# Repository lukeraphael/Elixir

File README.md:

# Elixir

The Elixir is a monoblock ergonomic mechanical keyboard. The design has been greatly inspired by the [Atreus](https://github.com/technomancy/atreus), [Sweep](https://github.com/davidphilipbarr/Sweep) and [Sofle](https://github.com/josefadamcik/SofleKeyboard) keyboards.

## Motivation

The Elixir was born out of a desire to create an 'introductory' ergonomic mechanical keyboard. Its simple and inexpensive construction reduces the time and cost required to get started. Furthermore, it was intentionally made to accomodate most common keycap sets, removing the need to obtain a niche 'ergo' keycap set.

## Features

- Powered by [QMK](https://docs.qmk.fm/#/)
- Fits many cheap standard keycap sets
  - Virtually all uniform profile sets e.g. DSA and XDA
  - Virtually all "full coverage" keycap sets
- 50 keys - just enough to accomodate to new users but few enough to allow users to experience layers, an imperative part of ergo keyboards

## Gallery

## Install firmware
Steps:
1. Copy qmk/keyboards/elixir to your local qmk folder
2. ```qmk flash -kb elixir -km default```
3. Plug in your micro controller and set it to flashing mode (connect reset and ground pins twice)

## License

The Elixir Keyboard is licensed under [Creative Commons Attribution-NonCommercial 4.0 International License](https://creativecommons.org/licenses/by-nc/4.0).

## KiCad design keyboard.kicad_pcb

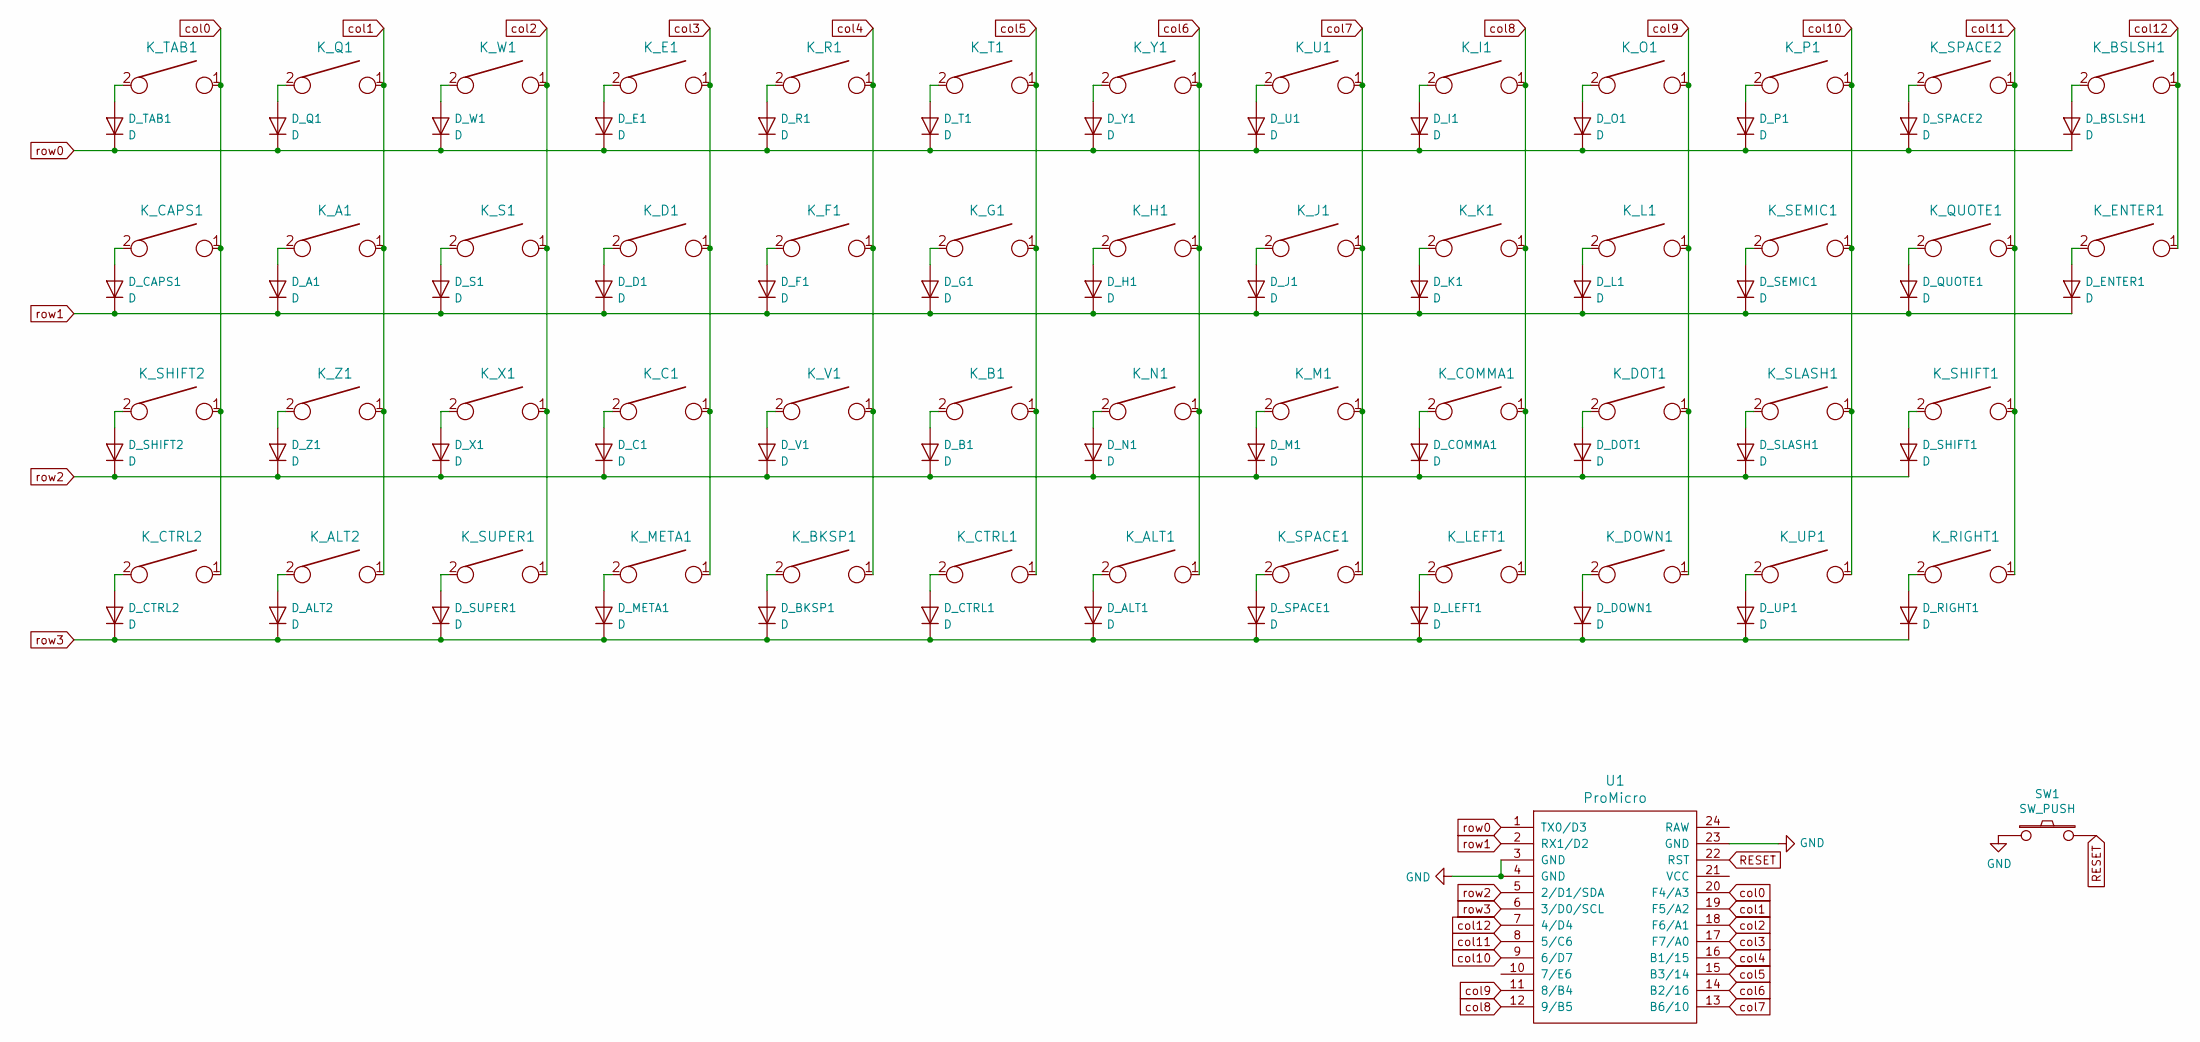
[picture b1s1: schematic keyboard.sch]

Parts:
D_A1: D; D_SOD123_axial
D_ALT1, D_ALT2: D; D_SOD123_axial
D_B1: D; D_SOD123_axial
D_BKSP1: D; D_SOD123_axial
D_BSLSH1: D; D_SOD123_axial
D_C1: D; D_SOD123_axial
D_CAPS1: D; D_SOD123_axial
D_COMMA1: D; D_SOD123_axial
D_CTRL1, D_CTRL2: D; D_SOD123_axial
D_D1: D; D_SOD123_axial
D_DOT1: D; D_SOD123_axial
D_DOWN1: D; D_SOD123_axial
D_E1: D; D_SOD123_axial
D_ENTER1: D; D_SOD123_axial
D_F1: D; D_SOD123_axial
D_G1: D; D_SOD123_axial
D_H1: D; D_SOD123_axial
D_I1: D; D_SOD123_axial
D_J1: D; D_SOD123_axial
D_K1: D; D_SOD123_axial
D_L1: D; D_SOD123_axial
D_LEFT1: D; D_SOD123_axial
D_M1: D; D_SOD123_axial
D_META1: D; D_SOD123_axial
D_N1: D; D_SOD123_axial
D_O1: D; D_SOD123_axial
D_P1: D; D_SOD123_axial
D_Q1: D; D_SOD123_axial
D_QUOTE1: D; D_SOD123_axial
D_R1: D; D_SOD123_axial
D_RIGHT1: D; D_SOD123_axial
D_S1: D; D_SOD123_axial
D_SEMIC1: D; D_SOD123_axial
D_SHIFT1, D_SHIFT2: D; D_SOD123_axial
D_SLASH1: D; D_SOD123_axial
D_SPACE1, D_SPACE2: D; D_SOD123_axial
D_SUPER1: D; D_SOD123_axial
D_T1: D; D_SOD123_axial
D_TAB1: D; D_SOD123_axial
D_U1: D; D_SOD123_axial
D_UP1: D; D_SOD123_axial
D_V1: D; D_SOD123_axial
D_W1: D; D_SOD123_axial
D_X1: D; D_SOD123_axial
D_Y1: D; D_SOD123_axial
D_Z1: D; D_SOD123_axial
K_A1: KEYSW; MX-1U
K_ALT1: KEYSW; MX-2U
K_ALT2: KEYSW; MX-1U
K_B1: KEYSW; MX-1U
K_BKSP1: KEYSW; MX-1.25U
K_BSLSH1: KEYSW; MX-1.5U
K_C1: KEYSW; MX-1U
K_CAPS1: KEYSW; MX-1.75U
K_COMMA1: KEYSW; MX-1U
K_CTRL1: KEYSW; MX-2U
K_CTRL2: KEYSW; MX-1.25U
K_D1: KEYSW; MX-1U
K_DOT1: KEYSW; MX-1U
K_DOWN1: KEYSW; MX-1U
K_E1: KEYSW; MX-1U
K_ENTER1: KEYSW; MX-2.25U
K_F1: KEYSW; MX-1U
K_G1: KEYSW; MX-1U
K_H1: KEYSW; MX-1U
K_I1: KEYSW; MX-1U
K_J1: KEYSW; MX-1U
K_K1: KEYSW; MX-1U
K_L1: KEYSW; MX-1U
K_LEFT1: KEYSW; MX-1U
K_M1: KEYSW; MX-1U
K_META1: KEYSW; MX-1U
K_N1: KEYSW; MX-1U
K_O1: KEYSW; MX-1U
K_P1: KEYSW; MX-1U
K_Q1: KEYSW; MX-1U
K_QUOTE1: KEYSW; MX-1U
K_R1: KEYSW; MX-1U
K_RIGHT1: KEYSW; MX-1U
K_S1: KEYSW; MX-1U
K_SEMIC1: KEYSW; MX-1U
K_SHIFT1: KEYSW; MX-2.75U
K_SHIFT2: KEYSW; MX-2.25U
K_SLASH1: KEYSW; MX-1U
K_SPACE1: KEYSW; MX-1.25U
K_SPACE2: KEYSW; MX-1U
K_SUPER1: KEYSW; MX-1U
K_T1: KEYSW; MX-1U
K_TAB1: KEYSW; MX-1.5U
K_U1: KEYSW; MX-1U
K_UP1: KEYSW; MX-1U
K_V1: KEYSW; MX-1U
K_W1: KEYSW; MX-1U
K_X1: KEYSW; MX-1U
K_Y1: KEYSW; MX-1U
K_Z1: KEYSW; MX-1U
SW1: SW_PUSH; ResetSW
U1: ProMicro; ProMicro_v3.5

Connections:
GND: SW1.1, U1.3 (GND), U1.4 (GND), U1.23 (GND)
unnamed: D_A1.2 (A), K_A1.2
unnamed: D_ALT1.2 (A), K_ALT1.2
unnamed: D_ALT2.2 (A), K_ALT2.2
unnamed: D_B1.2 (A), K_B1.2
unnamed: D_BKSP1.2 (A), K_BKSP1.2
unnamed: D_BSLSH1.2 (A), K_BSLSH1.2
unnamed: D_C1.2 (A), K_C1.2
unnamed: D_CAPS1.2 (A), K_CAPS1.2
unnamed: D_COMMA1.2 (A), K_COMMA1.2
unnamed: D_CTRL1.2 (A), K_CTRL1.2
unnamed: D_CTRL2.2 (A), K_CTRL2.2
unnamed: D_D1.2 (A), K_D1.2
unnamed: D_DOT1.2 (A), K_DOT1.2
unnamed: D_DOWN1.2 (A), K_DOWN1.2
unnamed: D_E1.2 (A), K_E1.2
unnamed: D_ENTER1.2 (A), K_ENTER1.2
unnamed: D_F1.2 (A), K_F1.2
unnamed: D_G1.2 (A), K_G1.2
unnamed: D_H1.2 (A), K_H1.2
unnamed: D_I1.2 (A), K_I1.2
unnamed: D_J1.2 (A), K_J1.2
unnamed: D_K1.2 (A), K_K1.2
unnamed: D_L1.2 (A), K_L1.2
unnamed: D_LEFT1.2 (A), K_LEFT1.2
unnamed: D_M1.2 (A), K_M1.2
unnamed: D_META1.2 (A), K_META1.2
unnamed: D_N1.2 (A), K_N1.2
unnamed: D_O1.2 (A), K_O1.2
unnamed: D_P1.2 (A), K_P1.2
unnamed: D_Q1.2 (A), K_Q1.2
unnamed: D_QUOTE1.2 (A), K_QUOTE1.2
unnamed: D_R1.2 (A), K_R1.2
unnamed: D_RIGHT1.2 (A), K_RIGHT1.2
unnamed: D_S1.2 (A), K_S1.2
unnamed: D_SEMIC1.2 (A), K_SEMIC1.2
unnamed: D_SHIFT1.2 (A), K_SHIFT1.2
unnamed: D_SHIFT2.2 (A), K_SHIFT2.2
unnamed: D_SLASH1.2 (A), K_SLASH1.2
unnamed: D_SPACE1.2 (A), K_SPACE1.2
unnamed: D_SPACE2.2 (A), K_SPACE2.2
unnamed: D_SUPER1.2 (A), K_SUPER1.2
unnamed: D_T1.2 (A), K_T1.2
unnamed: D_TAB1.2 (A), K_TAB1.2
unnamed: D_U1.2 (A), K_U1.2
unnamed: D_UP1.2 (A), K_UP1.2
unnamed: D_V1.2 (A), K_V1.2
unnamed: D_W1.2 (A), K_W1.2
unnamed: D_X1.2 (A), K_X1.2
unnamed: D_Y1.2 (A), K_Y1.2
unnamed: D_Z1.2 (A), K_Z1.2
RESET: SW1.2, U1.22 (RST)
col0: K_CAPS1.1, K_CTRL2.1, K_SHIFT2.1, K_TAB1.1, U1.20 (F4/A3)
col1: K_A1.1, K_ALT2.1, K_Q1.1, K_Z1.1, U1.19 (F5/A2)
col2: K_S1.1, K_SUPER1.1, K_W1.1, K_X1.1, U1.18 (F6/A1)
col3: K_C1.1, K_D1.1, K_E1.1, K_META1.1, U1.17 (F7/A0)
col4: K_BKSP1.1, K_F1.1, K_R1.1, K_V1.1, U1.16 (B1/15)
col5: K_B1.1, K_CTRL1.1, K_G1.1, K_T1.1, U1.15 (B3/14)
col6: K_ALT1.1, K_H1.1, K_N1.1, K_Y1.1, U1.14 (B2/16)
col7: K_J1.1, K_M1.1, K_SPACE1.1, K_U1.1, U1.13 (B6/10)
col8: K_COMMA1.1, K_I1.1, K_K1.1, K_LEFT1.1, U1.12 (9/B5)
col9: K_DOT1.1, K_DOWN1.1, K_L1.1, K_O1.1, U1.11 (8/B4)
col10: K_P1.1, K_SEMIC1.1, K_SLASH1.1, K_UP1.1, U1.9 (6/D7)
col11: K_QUOTE1.1, K_RIGHT1.1, K_SHIFT1.1, K_SPACE2.1, U1.8 (5/C6)
col12: K_BSLSH1.1, K_ENTER1.1, U1.7 (4/D4)
row0: D_BSLSH1.1 (K), D_E1.1 (K), D_I1.1 (K), D_O1.1 (K), D_P1.1 (K), D_Q1.1 (K), D_R1.1 (K), D_SPACE2.1 (K), D_T1.1 (K), D_TAB1.1 (K), D_U1.1 (K), D_W1.1 (K), D_Y1.1 (K), U1.1 (TX0/D3)
row1: D_A1.1 (K), D_CAPS1.1 (K), D_D1.1 (K), D_ENTER1.1 (K), D_F1.1 (K), D_G1.1 (K), D_H1.1 (K), D_J1.1 (K), D_K1.1 (K), D_L1.1 (K), D_QUOTE1.1 (K), D_S1.1 (K), D_SEMIC1.1 (K), U1.2 (RX1/D2)
row2: D_B1.1 (K), D_C1.1 (K), D_COMMA1.1 (K), D_DOT1.1 (K), D_M1.1 (K), D_N1.1 (K), D_SHIFT1.1 (K), D_SHIFT2.1 (K), D_SLASH1.1 (K), D_V1.1 (K), D_X1.1 (K), D_Z1.1 (K), U1.5 (2/D1/SDA)
row3: D_ALT1.1 (K), D_ALT2.1 (K), D_BKSP1.1 (K), D_CTRL1.1 (K), D_CTRL2.1 (K), D_DOWN1.1 (K), D_LEFT1.1 (K), D_META1.1 (K), D_RIGHT1.1 (K), D_SPACE1.1 (K), D_SUPER1.1 (K), D_UP1.1 (K), U1.6 (3/D0/SCL)

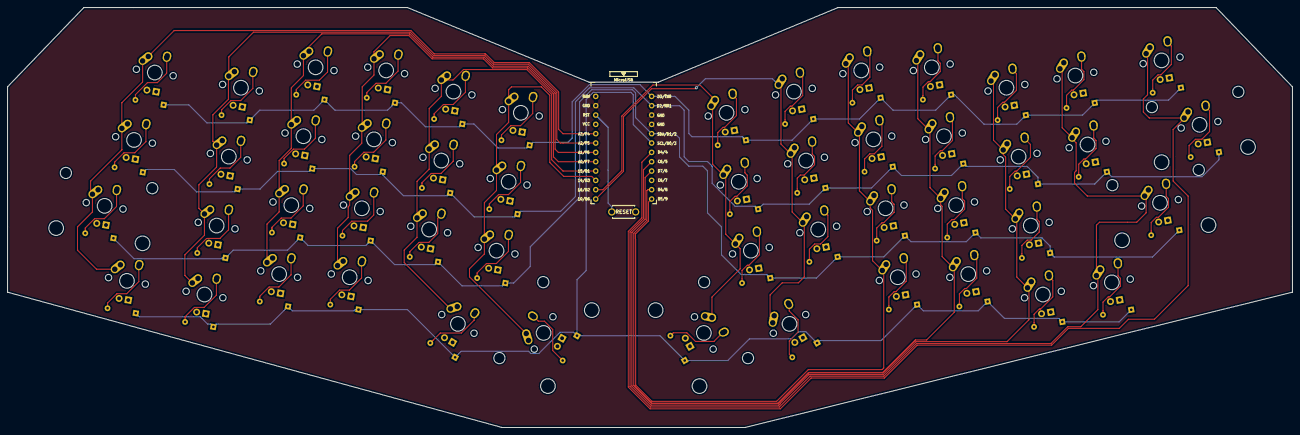
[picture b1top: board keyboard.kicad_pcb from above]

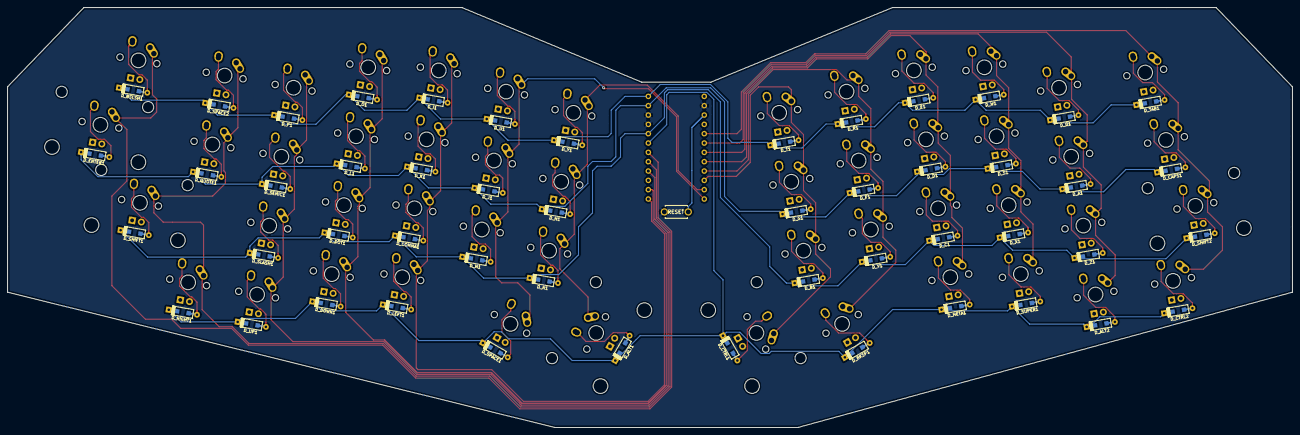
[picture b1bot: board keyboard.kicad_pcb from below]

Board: 2 copper layers, 349.7 x 114.3 mm, 102 parts (50 on the bottom side), 69 nets.

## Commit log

2022-04-10 init
2022-04-10 add libraries
2022-04-10 add pro micro
2022-04-10 removed atmega and updated schematic with promicro
2022-04-11 aligned switches
2022-04-11 aligned all components
2022-04-12 complete routing
2022-04-12 add reset switch and ground zones
2022-04-12 add license
2022-04-12 add images
2022-04-12 add readme
2022-04-12 restructure project
2022-04-12 add firmware
2022-04-15 remove zones and reroute ground
2022-04-15 add gerbers
2022-04-16 clean up routes
2022-04-16 generate gerber
2022-08-07 chore: remove .DS_store
2022-08-07 docs: add product image
2022-08-07 feat: add firmware files
2022-08-07 docs: add qmk installation instructions
